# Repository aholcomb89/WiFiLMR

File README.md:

# WiFiLMR
Subscriber unit that communications via WiFi

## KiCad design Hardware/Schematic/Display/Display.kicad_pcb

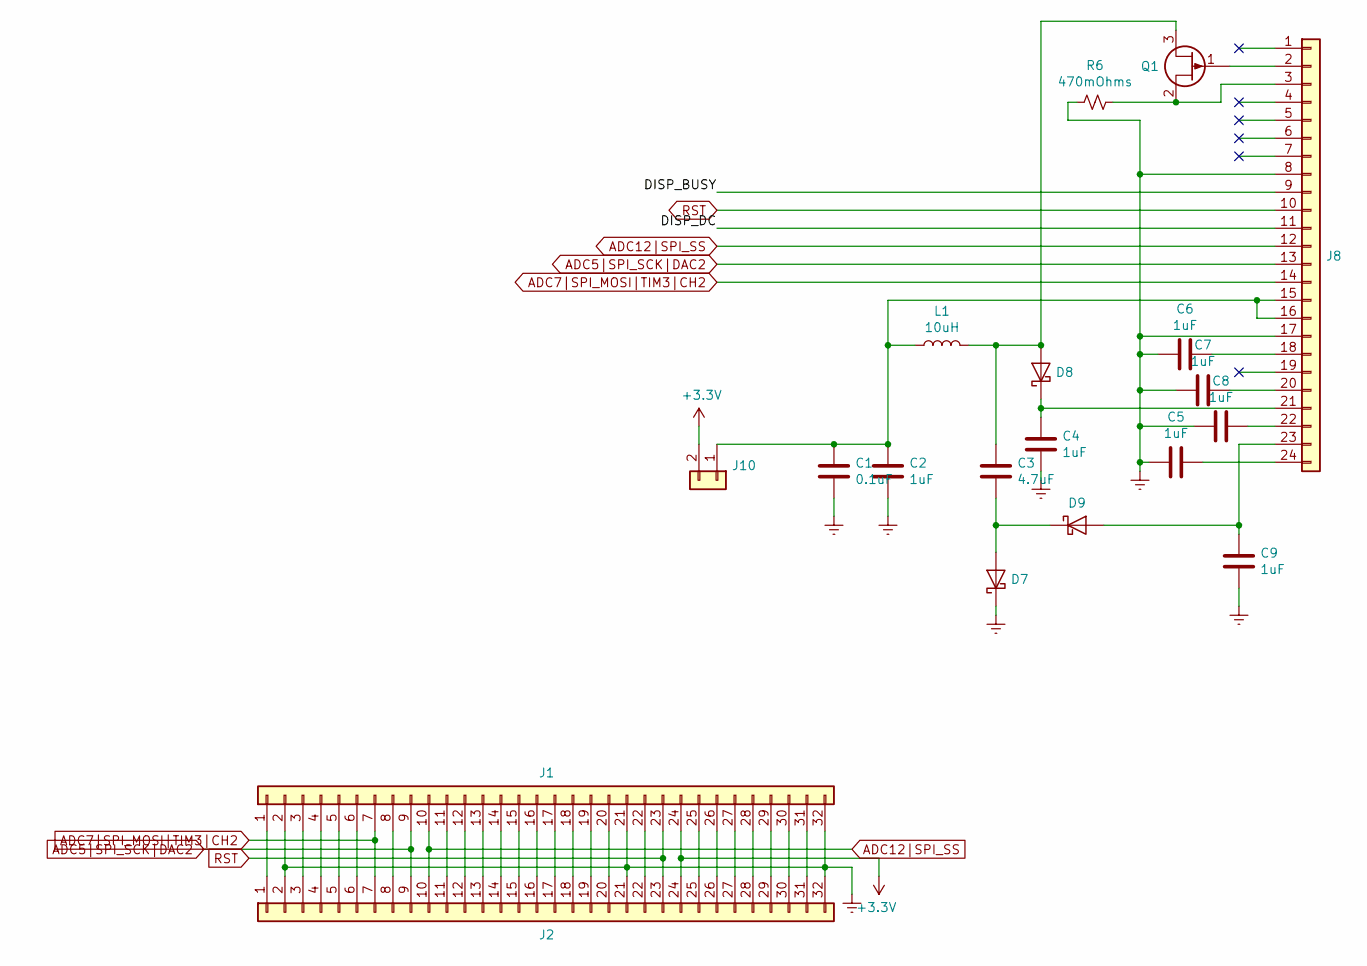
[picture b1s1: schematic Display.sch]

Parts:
C1: 0.1uF; C_2512_6332Metric_Pad1.52x3.35mm_HandSolder
C2, C4, C5, C6, C7, C8, C9: 1uF; C_2512_6332Metric_Pad1.52x3.35mm_HandSolder
C3: 4.7uF; C_2512_6332Metric_Pad1.52x3.35mm_HandSolder
D7, D8, D9: D_Schottky; D_2512_6332Metric_Pad1.52x3.35mm_HandSolder
J1: Conn_01x32; PinHeader_2x16_P2.54mm_Horizontal
J2: Conn_01x32; PinSocket_2x16_P2.54mm_Horizontal
J8: Conn_01x24; Hirose_FH12-24S-0.5SH_1x24-1MP_P0.50mm_Horizontal
J10: Conn_01x02; PinHeader_1x02_P2.54mm_Vertical
L1: 10uH; L_2512_6332Metric_Pad1.52x3.35mm_HandSolder
Q1: Q_PJFET_GSD; SOT-23
R6: 470mOhms; R_2512_6332Metric_Pad1.52x3.35mm_HandSolder

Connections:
+3V3: J1.24, J2.24, J10.2
/DISP_BUSY: J8.9
/DISP_DC: J8.11
ADC5|SPI_SCK|DAC2: J1.9, J2.9, J8.13
ADC7|SPI_MOSI|TIM3|CH2: J1.7, J2.7, J8.14
ADC12|SPI_SS: J1.10, J2.10, J8.12
Earth: C1.2, C2.2, C4.2, C5.1, C6.1, C7.1, C8.1, C9.2, D7.1 (K), J1.2, J1.21, J1.32, J2.2, J2.21, J2.32, J8.8, J8.17, R6.1
unnamed: C1.1, C2.1, J8.15, J8.16, J10.1, L1.1
unnamed: C3.1, D8.2 (A), L1.2, Q1.3 (D)
unnamed: C3.2, D7.2 (A), D9.1 (K)
unnamed: C4.1, D8.1 (K), J8.21
unnamed: C5.2, J8.24
unnamed: C6.2, J8.18
unnamed: C7.2, J8.20
unnamed: C8.2, J8.22
unnamed: C9.1, D9.2 (A), J8.23
unnamed: J1.1, J2.1
unnamed: J1.3, J2.3
unnamed: J1.4, J2.4
unnamed: J1.5, J2.5
unnamed: J1.6, J2.6
unnamed: J1.8, J2.8
unnamed: J1.11, J2.11
unnamed: J1.12, J2.12
unnamed: J1.13, J2.13
unnamed: J1.14, J2.14
unnamed: J1.15, J2.15
unnamed: J1.16, J2.16
unnamed: J1.17, J2.17
unnamed: J1.18, J2.18
unnamed: J1.19, J2.19
unnamed: J1.20, J2.20
unnamed: J1.22, J2.22
unnamed: J1.25, J2.25
unnamed: J1.26, J2.26
unnamed: J1.27, J2.27
unnamed: J1.28, J2.28
unnamed: J1.29, J2.29
unnamed: J1.30, J2.30
unnamed: J1.31, J2.31
unnamed: J8.2, Q1.1 (G)
unnamed: J8.3, Q1.2 (S), R6.2
RST: J1.23, J2.23, J8.10

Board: 2 copper layers, 19 parts (0 on the bottom side), 41 nets, no tracks yet.

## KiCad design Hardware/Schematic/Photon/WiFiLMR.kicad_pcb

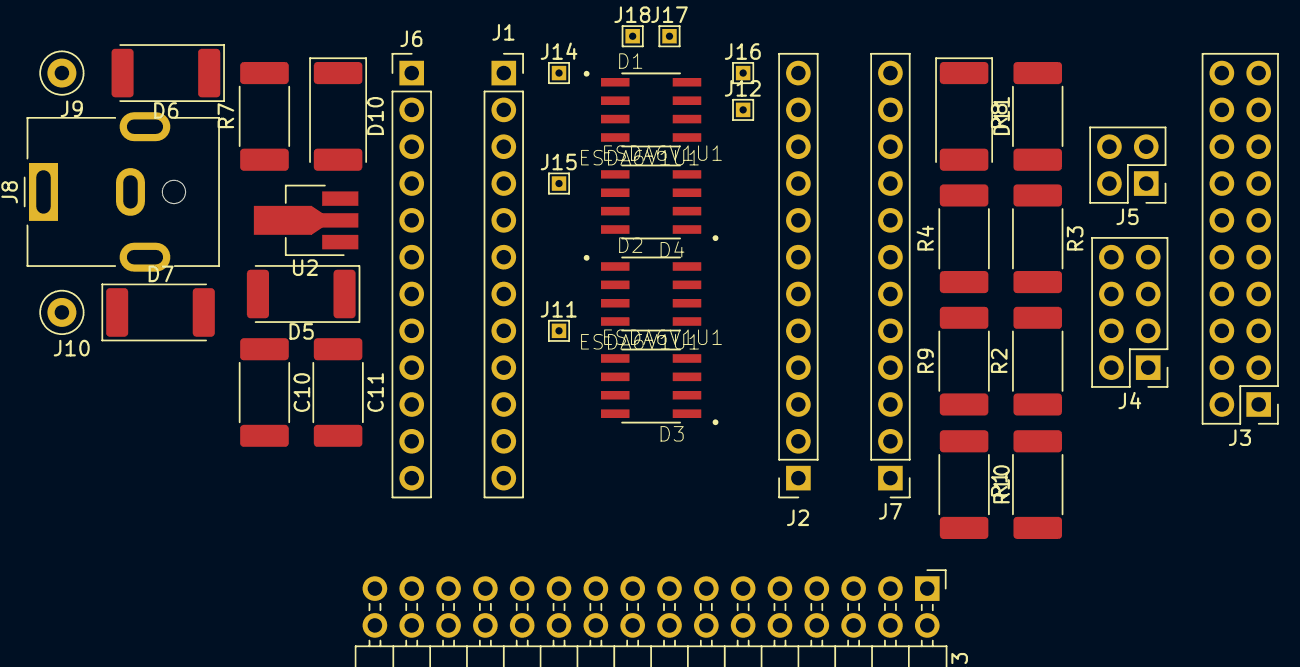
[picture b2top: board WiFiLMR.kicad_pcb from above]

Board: 2 copper layers, 38 parts (0 on the bottom side), 43 nets, no tracks yet.

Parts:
C10, C11: 1uF; C_2512_6332Metric_Pad1.52x3.35mm_HandSolder
D1, D2, D3, D4: ESDA6V1U1; SOIC127P600X175-8N
D5, D6, D7: D; D_2512_6332Metric_Pad1.52x3.35mm_HandSolder
D10, D11: LED; D_2512_6332Metric_Pad1.52x3.35mm_HandSolder
J1, J2: Conn_01x12; PinSocket_1x12_P2.54mm_Vertical
J3: JTAG; PinHeader_2x10_P2.54mm_Vertical
J4: Conn_02x04_Odd_Even; PinHeader_2x04_P2.54mm_Vertical
J5: Conn_02x02_Odd_Even; PinHeader_2x02_P2.54mm_Vertical
J6, J7: Conn_01x12; PinHeader_1x12_P2.54mm_Vertical
J8: Barrel_Jack_MountingPin; BarrelJack_CUI_PJ-063AH_Horizontal
J9, J10: Conn_01x01; TestPoint_Loop_D2.50mm_Drill1.0mm
J11, J12, J14, J15, J16, J17, J18: Conn_01x01; TestPoint_THTPad_1.0x1.0mm_Drill0.5mm
J13: Conn_01x32; PinHeader_2x16_P2.54mm_Horizontal
R1, R2, R3, R4, R7, R8, R9, R10: R_Small_US; R_2512_6332Metric_Pad1.52x3.35mm_HandSolder
U2: L7805; SOT-89-3_Handsoldering

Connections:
+3V3: D4.8, D11.1, J2.12, J3.1, J7.12, J13.24, R1.1, R2.1, R3.1, R9.2, R10.2
+5V: C11.1, D1.1, D10.1, J1.1, J6.1, J13.1, U2.3
+BATT: D4.4, J2.10, J7.10, J13.22
ADC4|DAC1: D1.8, J1.6, J6.6, J13.6
ADC5|SPI_SCK|DAC2: D2.3, J1.9, J6.9, J13.9
ADC6|SPI_MISO|TIM3_CH1: D2.2, J1.8, J6.8, J13.8
ADC7|SPI_MOSI|TIM3|CH2: D2.1, J1.7, J6.7, J13.7
ADC12|SPI_SS: D2.4, J1.10, J6.10, J13.10
ADC13: D2.5, J1.11, J6.11, J13.11
ADC15: J1.12, J13.12
Earth: C10.2, C11.2, D1.2, D4.3, D7.2, J1.2, J2.9, J3.4, J3.6, J3.8, J3.10, J3.11, J3.12, J3.14, J3.16, J3.18, J3.20, J6.2, J7.9, J8.2, J13.2, J13.21, J13.32, R4.1, R7.2, R8.2, U2.2
JTAG_TCK: D4.1, J2.7, J4.7, J7.7, J13.19
JTAG_TDI|SPI1_SS|I2S3_WS: D3.8, J2.6, J4.3, J7.6, J13.18
JTAG_TDO|SPI1_SCK|I2S3_SCK: D3.5, J2.5, J5.1, J7.5, J13.17
JTAG_TMS: D4.2, J2.8, J4.5, J7.8, J13.20
JTAG_TRST|SPI1_MISO|TIM3_CH1: D3.4, J2.4, J4.1, J7.4, J13.16
unnamed: C10.1, D5.1, D6.1, U2.1
unnamed: D2.8, J6.12
unnamed: D5.2, J8.1
unnamed: D6.2, J9.1
unnamed: D7.1, J10.1
unnamed: D10.2, R7.1
unnamed: D11.2, R8.1
unnamed: J3.3, J4.2, R1.2
unnamed: J3.5, J4.4, R2.2
unnamed: J3.7, J4.6, R3.2
unnamed: J3.9, J4.8, R4.2
unnamed: J3.13, J5.2
unnamed: J3.15, J5.4
RGB_BLUE: J13.29, J16.1
RGB_GREEN: J12.1, J13.28
RGB_RED: J11.1, J13.27
RST: D4.5, J2.11, J5.3, J7.11, J13.23
SCL|CAN2_TX|TIM4_CH1: D3.2, J2.2, J7.2, J13.14, R9.1
SDA|TIM4_CH2: D3.1, J2.1, J7.1, J13.13, R10.1
SETUP_BUTTON: J13.26, J15.1
SMPS_ENABLE: J13.25, J14.1
SPI1_MOSI|CAN2_RX|TIM3_CH2|I2S3_SD: D3.3, J2.3, J7.3, J13.15
USART1_RX|TIM1_CH3: D1.4, J1.4, J6.4, J13.4
USART1_TX|TIM1_CH2: D1.3, J1.3, J6.3, J13.3
USB_DATA+: J13.31, J18.1
USB_DATA-: J13.30, J17.1
WKUP|ADC0|TIM5_CH1: D1.5, J1.5, J6.5, J13.5

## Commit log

2019-06-02 Part selection directory structure with initial Cypress WiFi module and Microchip SAM4E/S datasheets
2019-06-03 Schematic sandbox
    Added schematic and pcb layout for basic ESP32-WROOM-32D module.
2019-06-05 Particle Photon Schematic Update
    Added Particle Photon symbol, footprint & 3D model along with datasheet. Updated schematic with sockets to plugin a Photon board and a JTAG connector based off of the design in the Photon datasheet.
2019-06-05 Update fp-info-cache
2019-06-08 Update schematic with JTAG and debug headers
2019-06-08 Added TCA8418 keyscan module to the schematic
2019-06-08 Added E-INK display connector and datasheet
2019-06-10 Lots of schematic updates
    Lots of stuff...
    * Added a new 8-pin TVS diode array
    * Finalized the display connector
    * Corrected the net labels to global labels so they span across sheets
    * Added a 5V linear voltage regulator and LEDs to debug power
2019-06-15 Added pogo-pin test points for "Extra" photon lines. Also added a 32-pin vertical header for connecting multiple smaller boards.
2019-06-15 Misc changes I forgot to commit.
2019-06-16 Split-up schematics into three seperate projects with a parts library as well
2019-06-16 Added a barrel jack connector to the photon board
2019-06-16 Updated keypad and display schematic to use header sockets for intra-board connections.
2019-06-16 Added male 02x16 header to auxillary boards so they can be "stacked" together
2019-06-22 Added footprint & symbol for ATWINC1500
2019-06-22 ATWINC15x0 datasheets
2019-06-23 Added STM32L496xx datasheet and added symbol to schematic
2019-06-26 Added FreeRTOS v10.2.1
2019-06-26 Added TI TivaWare (temporary)
2019-06-26 Added libopus 1.3.1
2019-06-26 Added skeleton files from tiva-gcc-base
2019-06-26 Added TI's UARTStdio library (temporary)
2019-07-10 Opus+FreeRTOS benchmark demo.
2019-07-10 Added datasheet for STM32L452RE
2019-07-24 Removed TivaWare and UARTStdio (TI stuff)
2019-07-24 Adjust linker script for STM32L452RE
2019-07-24 Trimmed remaining references to TivaWare
2019-07-24 Added initial HAL components
2019-07-24 Updated main and Makefile
    The opus demo is disabled for now until the clock speed is increased and
    logging is implemented.
2019-07-28 Added a custom printf-like mechanism
2019-07-28 Added basic logging via picofmt
2019-07-29 Replaced spin loops with asm to prevent optimization
2019-07-29 Fixed an issue with logging with no parameters
2019-07-29 Added more unit literals
2019-07-29 Fixed ClockDevices base case
2019-07-29 Shift the result of getRegBits over to match bit-banding version
2019-07-30 Added clock speed adjustment (4 & 80 MHz)
2019-08-03 Initial FreeRTOS config on STM32
2019-08-03 Fixed an multiplication overflow in setBaudRate
    80Mhz * 256 takes about 35 bits to express, so the UART was broken
    after increasing the clock speed.
2019-08-03 Made interrupt vector table debugging optional
2019-08-17 File extension changes: project.bin => project.elf main.axf => main.bin
    These allow the ST-LINK flash utilities to correctly interpret the files.
    Also slightly modified the Makefile to allow for different toolchains (default to arm-none-eabi-).wqq
2019-08-21 Added initial SPI driver
2019-08-21 Made GPIO AltFunc enum general
2019-08-21 Converted HAL::LPUART to use inline static variable
2019-08-21 Made SPI driver check TXE instead of FTLVL for pioWrite
    This should make it easier to toggle slave selects at the right times.
2019-08-21 Added SPI driver demo task
2019-08-28 Initial DAC driver (untested)
2019-08-28 Initial DMA driver (untested)
2019-08-28 Added more devices to RCC driver
2019-08-28 Initial timer driver (untested)
    Only support for TIM6 was implemented. I plan on hiding the features of
    more advanced timers behind std::enable_if when support for those is
    added
2019-08-28 Added a basic way to set ISRs on the fly (untested)
2019-08-28 Added a DAC/Timer/DMA demo that outputs a sine wave (untested)
2019-09-04 Added DAC software trigger method
2019-09-04 Added DMA direction control
2019-09-04 Fixed a typo in RCC driver
2019-09-04 Fixed DAC/DMA example (and disabled SPI example)
